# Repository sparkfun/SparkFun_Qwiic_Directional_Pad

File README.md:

SparkFun Qwiic Directional Pad
========================================

[*SparkFun Qwiic Directional Pad (PRT-26851)*](https://www.sparkfun.com/products/26851)

<Basic description of the part.>

Repository Contents
-------------------

* **.github/workflows** - YAML files used for GitHub Actions and GitHub Pages/mkdocs
* **/Firmware** - Example code
* **/Hardware** - KiCad design files (.kicad_pcb, .kicad_sch, .kicad_pro)
* **/docs** - Online documentation files
  * **/assets** - Folder containing all the file assets used for product documentation
    * **/3d_model** - Exported 3D models from KiCad
    * **/board_files** - Copy of design files used for product documentation
    * **/component_documentation** - Datasheets and manuals for hardware components
    * **/img** - Images for product documentation
  * **/github** - Files stating how to contribute and filing issues used for product documentation
  * **/javascript** - Folder containing custom javascript used for product documentation
  * **/stylesheet** - Folder containing CSS files used for product documentation
* **/overrides** - Customization files used for product documentation
  * **/.icons** - Icons used for GitHub used for product documentation
  * **./partials** - Used for product documentation

Documentation
--------------
* **[Library](https://github.com/sparkfun/SparkFun_I2C_Expander_Arduino_Library)** - Arduino library for the Qwiic Directional Pad.
* **[Hookup Guide](https://docs.sparkfun.com/SparkFun_Qwiic_Directional_Pad/)** - Basic hookup guide for the Qwiic Directional Pad.

Product Versions
----------------
* [PRT-26851](https://www.sparkfun.com/products/26851) - v1.1

Version History
---------------
* v1.1 - Initial Release

License Information
-------------------

This product is _**open source**_! 

Please review the LICENSE.md file for license information. 

If you have any questions or concerns on licensing, please contact technical support on our [SparkFun forums](https://forum.sparkfun.com/viewforum.php?f=152).

Distributed as-is; no warranty is given.

- Your friends at SparkFun.

_<COLLABORATION CREDIT>_

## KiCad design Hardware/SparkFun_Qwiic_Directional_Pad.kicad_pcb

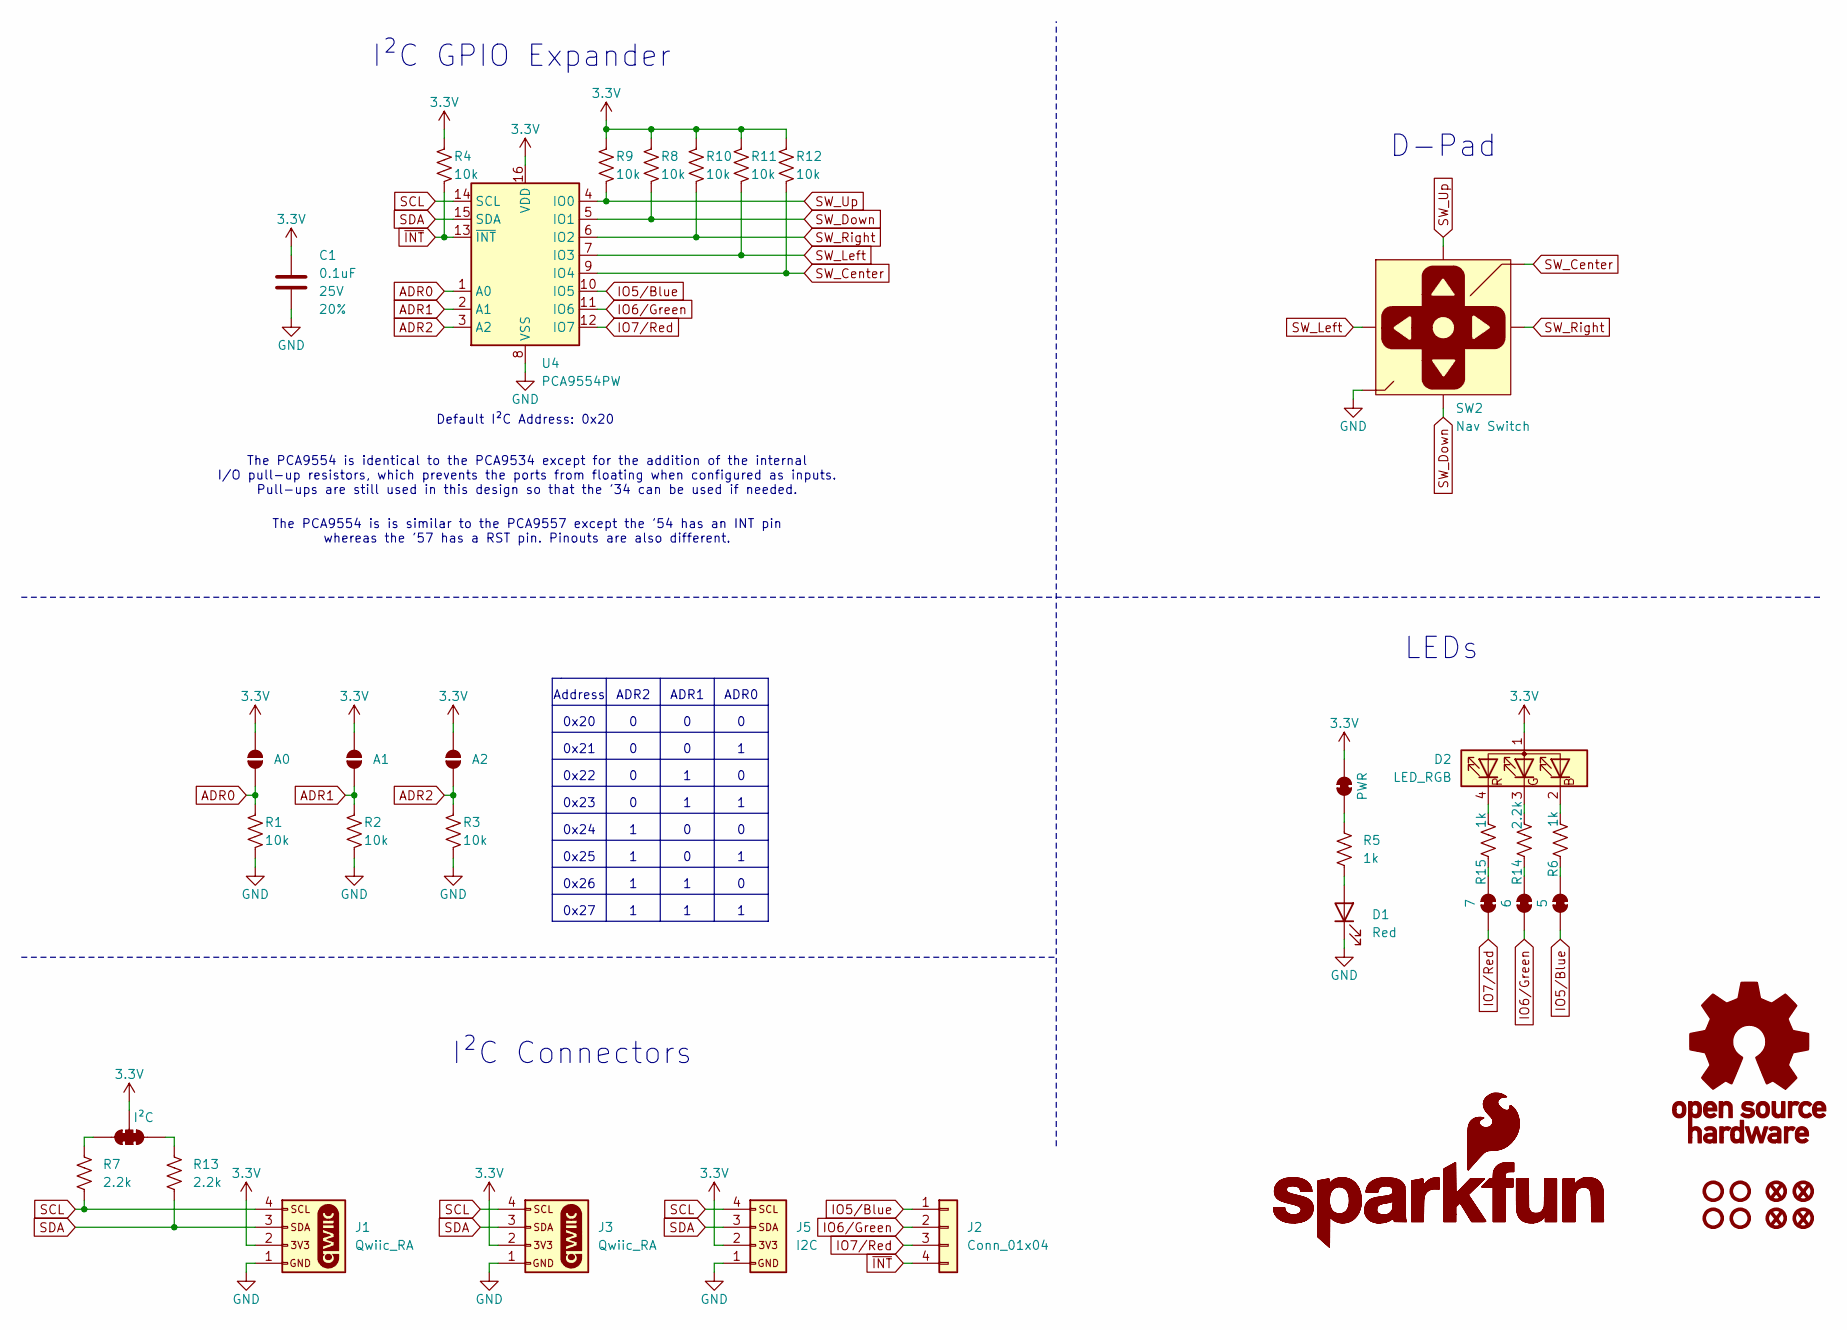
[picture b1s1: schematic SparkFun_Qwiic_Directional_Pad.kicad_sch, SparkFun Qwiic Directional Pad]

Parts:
C1: 0.1uF; C_0603_1608Metric; Voltage 25V; Tolerance 20%
D1: Red; LED_0603_1608Metric_Red
D2: LED_RGB; LED_1205_RGB_Bottom
FID1, FID2, FID3, FID4: Fiducial_0.5mm; Fiducial_0.5mm_Mask1mm
G1: OSHW_Logo; Creative_Commons_License
G3: SparkFun_Logo
G5: SparkFun_Logo; SparkFun_Logo_8mm
J1, J3: Qwiic_RA; JST_SMD_1.0mm-4_RA
J2: Conn_01x04; 1x04
J5: I2C; 1x04
JP1: A0; Jumper_2_NO
JP2: A1; Jumper_2_NO
JP3: A2; Jumper_2_NO
JP4: PWR; Jumper_2_NC_Trace
JP5: 5; Jumper_2_NC_Trace
JP6: I²C; Jumper_3_NC-2_Trace
JP7: 6; Jumper_2_NC_Trace
JP8: 7; Jumper_2_NC_Trace
R1, R2, R3, R4, R8, R9, R10, R11, R12: 10k; R_0603_1608Metric
R5, R6, R15: 1k; R_0603_1608Metric
R7, R13, R14: 2.2k; R_0603_1608Metric
ST1, ST2, ST3, ST4: Standoff
SW2: Nav Switch; Navigation_SMD_9.9x9.9mm
U4: PCA9554PW; TSSOP-16_4.4x5mm_P0.65mm

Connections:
3.3V: C1.1, D2.1 (A), J1.2, J3.2, J5.2, JP1.2 (B), JP2.2 (B), JP3.2 (B), JP4.2 (B), JP6.2 (C), R4.2, R8.2, R9.2, R10.2, R11.2, R12.2, U4.16 (VDD)
ADR0: JP1.1 (A), R1.2, U4.1 (A0)
ADR1: JP2.1 (A), R2.2, U4.2 (A1)
ADR2: JP3.1 (A), R3.2, U4.3 (A2)
GND: C1.2, D1.1 (K), J1.1, J3.1, J5.1, R1.1, R2.1, R3.1, SW2.3 (GND), SW2.6 (GND), SW2.8 (GND), SW2.9 (GND), SW2.10 (GND), U4.8 (VSS)
IO5/Blue: J2.1, JP5.2 (B), U4.10 (IO5)
IO6/Green: J2.2, JP7.2 (B), U4.11 (IO6)
IO7/Red: J2.3, JP8.2 (B), U4.12 (IO7)
unnamed: D1.2 (A), R5.2
unnamed: D2.2 (BK), R6.2
unnamed: D2.3 (GK), R14.2
unnamed: D2.4 (RK), R15.2
unnamed: JP4.1 (A), R5.1
unnamed: JP5.1 (A), R6.1
unnamed: JP6.1 (A), R13.1
unnamed: JP6.3 (B), R7.1
unnamed: JP7.1 (A), R14.1
unnamed: JP8.1 (A), R15.1
SCL: J1.4, J3.4, J5.4, R7.2, U4.14 (SCL)
SDA: J1.3, J3.3, J5.3, R13.2, U4.15 (SDA)
SW_Center: R12.1, SW2.4 (Center), U4.9 (IO4)
SW_Down: R8.1, SW2.5 (Down), U4.5 (IO1)
SW_Left: R11.1, SW2.7 (Left), U4.7 (IO3)
SW_Right: R10.1, SW2.2 (Right), U4.6 (IO2)
SW_Up: R9.1, SW2.1 (Up), U4.4 (IO0)
~INT: J2.4, R4.1, U4.13 (~INT)

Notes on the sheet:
The PCA9554 is is similar to the PCA9557 except the '54 has an INT pin whereas the '57 has a RST pin. Pinouts are also different.
Default I²C Address: 0x20
I²C GPIO Expander
0x20
I²C Connectors
ADR2
ADR0
0x23
The PCA9554 is identical to the PCA9534 except for the addition of the internal I/O pull-up resistors, which prevents the ports from floating when configured as inputs. Pull-ups are still used in this design so that the '34 can be used if needed.
0x22
LEDs
0x25
0x26
0x24
D-Pad
0x27
ADR1
0x21
Address

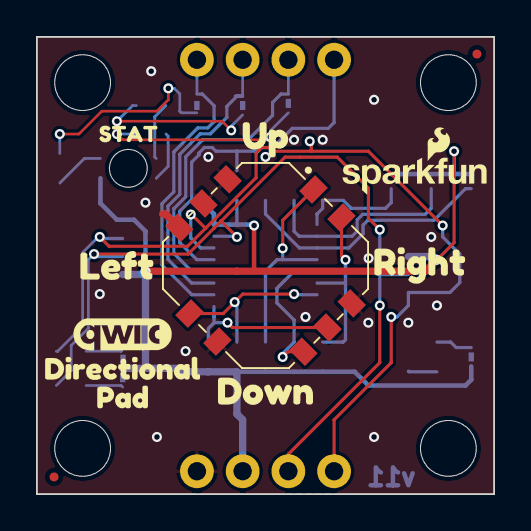
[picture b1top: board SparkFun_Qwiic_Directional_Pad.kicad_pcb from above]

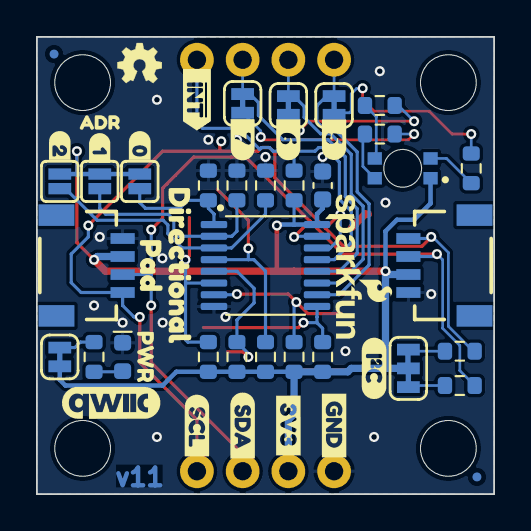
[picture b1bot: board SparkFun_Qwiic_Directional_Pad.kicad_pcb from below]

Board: 2 copper layers, 25.4 x 25.4 mm, 65 parts (48 on the bottom side), 26 nets.

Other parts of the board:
Ref**: Val**; OSHW_Logo_2.5mm
kibuzzard-64C2E6A3: G***; kibuzzard-64C2E6A3
kibuzzard-66EED5D2: G***; kibuzzard-66EED5D2
kibuzzard-66EF6B89: G***; kibuzzard-66EF6B89
kibuzzard-66EF7A0B: G***; kibuzzard-66EF7A0B
kibuzzard-66EF7A03: G***; kibuzzard-66EF7A03
kibuzzard-66EF7A24: G***; kibuzzard-66EF7A24
kibuzzard-66EF7AE6: G***; kibuzzard-66EF7AE6
kibuzzard-66EF7AEF: G***; kibuzzard-66EF7AEF
kibuzzard-66EF7B1E: G***; kibuzzard-66EF7B1E
kibuzzard-66EF7B7C, kibuzzard-66EF7B7C#2: G***; kibuzzard-66EF7B7C
kibuzzard-66EF7B15: G***; kibuzzard-66EF7B15
kibuzzard-66EF7B78, kibuzzard-66EF7B78#2: G***; kibuzzard-66EF7B78
kibuzzard-66EF55AC: G***; kibuzzard-66EF55AC
kibuzzard-66EF79E9: G***; kibuzzard-66EF79E9
kibuzzard-66EF559E: G***; kibuzzard-66EF559E
kibuzzard-66EF5597: G***; kibuzzard-66EF5597
kibuzzard-66F18F5E: G***; kibuzzard-66F18F5E
kibuzzard-66F18F8F: G***; kibuzzard-66F18F8F
kibuzzard-66F18F9B: G***; kibuzzard-66F18F9B
kibuzzard-66F182A6: G***; kibuzzard-66F182A6
kibuzzard-67117BDD: G***; kibuzzard-67117BDD

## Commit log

2024-09-23 Add ignore
2024-09-23 Fix page names.
2024-09-23 Add DRC exclusions
2024-09-23 Switch to RGB 1205 rear mount LED
2024-10-08 Switch to PCA9554
2024-10-08 Add test firmware
2024-10-17 Switch to PCA9554 with INT pin
2024-10-17 Update jumper names, I2C address table.
2024-11-18 Add example sketch
2024-11-19 Initial GitHub Pages Push
2024-11-19 Delete Copies of Datasheets
    - The contents of the Documents folder were moved to ../docs/assets/component_documentation. Removing the extra copies.
2024-11-21 Remove PCA9557
    Since we are using the PCA9554 instead of PCA9557
    - Remove PCA9557 Datasheet
    - Update Serial Output Message
2024-11-21 Add More Content
    - Introduction
    - Hardware Overview
    - Hardware Hookup
    - Arduino Library
    - Tutorial Photos
2024-11-22 Add Arduino Example, Fix Typos, & Remove Artifacts from Cloned Tutorial
2024-11-22 Fix Typos and Add Interrupt Example
2024-11-25 Rename Files
2024-11-25 Remove old PCA9557 code
2024-11-25 Update Example 1 in tutorial and Add Example 2
2024-11-25 Update Section Name
2024-11-26 Fix Typos and Add Reference Tables
2024-11-27 Add Note about Interrupt Pin
2024-12-02 Deployed 545eb8c with MkDocs version: 1.6.1
2024-12-03 Deployed bbbb396 with MkDocs version: 1.6.1
2024-12-04 Deployed 6687753 with MkDocs version: 1.6.1
2025-01-29 Deployed 471da07 with MkDocs version: 1.6.1

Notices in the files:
parts and their libraries:
https://creativecommons.org/licenses/by-sa/4.0
Released under the Creative Commons Attribution Share-Alike 4.0 License
